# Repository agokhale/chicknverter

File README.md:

# chicknverter
high voltage pwm output stage

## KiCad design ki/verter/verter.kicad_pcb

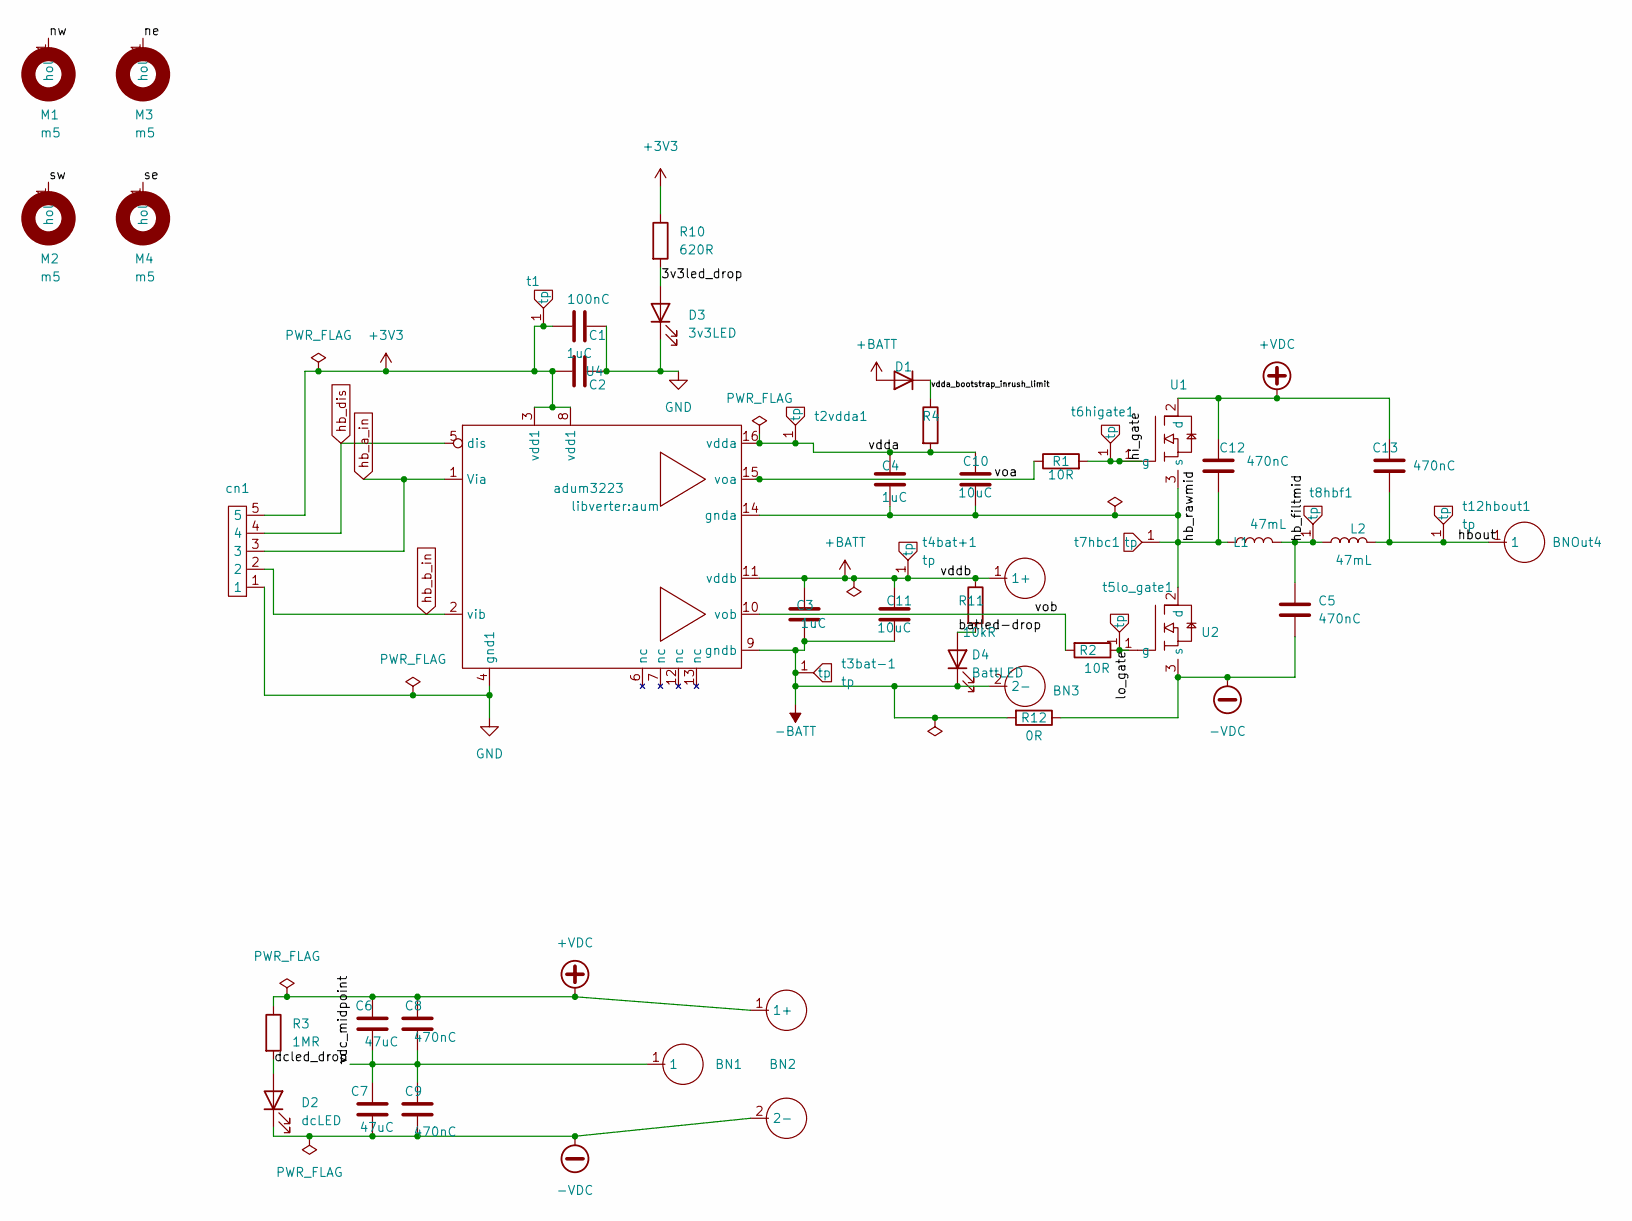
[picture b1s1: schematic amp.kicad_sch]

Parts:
BN1: bana_1; bannaone
BN2, BN3: bana; bannahammuk
BNOut4: bana_1; bannaone
C1: 100nC; C_0603_1608Metric_Pad1.08x0.95mm_HandSolder
C2: 1uC; bettrsmt_polar
C3, C4: 1uC; C_0603_1608Metric_Pad1.08x0.95mm_HandSolder
C5, C8, C9, C12, C13: 470nC; C_2220_5650Metric_Pad1.97x5.40mm_HandSolder
C6, C7: 47uC; epcos-d-25
C10, C11: 10uC; bettrsmt_polar
D1: D; bettrsmt_diode
D2: dcLED; bettrsmt_diode
D3: 3v3LED; bettrsmt_diode
D4: BattLED; bettrsmt_diode
L1, L2: 47mL; Lish
M1, M2, M3, M4: m5; m5mount
R1, R2: 10R; bettrsmt
R3: 1MR; C_0603_1608Metric_Pad1.08x0.95mm_HandSolder
R4: 27R; bettrsmt
R10: 620R; C_0603_1608Metric_Pad1.08x0.95mm_HandSolder
R11: 10kR; C_0603_1608Metric_Pad1.08x0.95mm_HandSolder
R12: 0R; bettrsmt
U1, U2: (no value)
U4: adum3223; aum
cn1: jumper5; jumper.1x5
t1, t2vdda1, t3bat-1, t4bat+1, t5lo_gate1, t6higate1, t7hbc1, t8hbf1, t12hbout1: tp

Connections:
+3V3: C1.1, C2.1, R10.1, U4.3 (vdd1), U4.8 (vdd1), cn1.5, t1.1 (tp)
+BATT: BN3.1 (1+), C3.1, C11.1, D1.2 (A), R11.1, U4.11 (vddb), t4bat+1.1 (tp)
+VDC: BN2.1 (1+), C6.1, C8.1, C12.1, C13.1, R3.1, U1.2 (d)
-BATT: BN3.2 (2-), C3.2, C11.2, D4.1 (K), R12.2, U4.9 (gndb), t3bat-1.1 (tp)
-VDC: BN2.2 (2-), C5.2, C7.2, C9.2, D2.1 (K), R12.1, U2.3 (s)
/amp/3v3led_drop: D3.2 (A), R10.2
/amp/batled-drop: D4.2 (A), R11.2
/amp/dcled_drop: D2.2 (A), R3.2
/amp/hb_filtmid: C5.1, L1.2, L2.1, t8hbf1.1 (tp)
/amp/hb_rawmid: C4.2, C10.2, C12.2, L1.1, U1.3 (s), U2.2 (d), U4.14 (gnda), t7hbc1.1 (tp)
/amp/hbout: BNOut4.1, C13.2, L2.2, t12hbout1.1 (tp)
/amp/hi_gate: R1.2, U1.1 (g), t6higate1.1 (tp)
/amp/lo_gate: R2.1, U2.1 (g), t5lo_gate1.1 (tp)
/amp/ne: M3.1 (hol)
/amp/nw: M1.1 (hol)
/amp/se: M4.1 (hol)
/amp/sw: M2.1 (hol)
/amp/vdc_midpoint: BN1.1, C6.2, C7.1, C8.2, C9.1
/amp/vdda: C4.1, C10.1, R4.2, U4.16 (vdda), t2vdda1.1 (tp)
/amp/vdda_bootstrap_inrush_limit: D1.1 (K), R4.1
/amp/voa: R1.1, U4.15 (voa)
/amp/vob: R2.2, U4.10 (vob)
GND: C1.2, C2.2, D3.1 (K), U4.4 (gnd1), cn1.1
hb_a_in: U4.1 (Via), cn1.3
hb_b_in: U4.2 (vib), cn1.2
hb_dis: U4.5 (dis), cn1.4

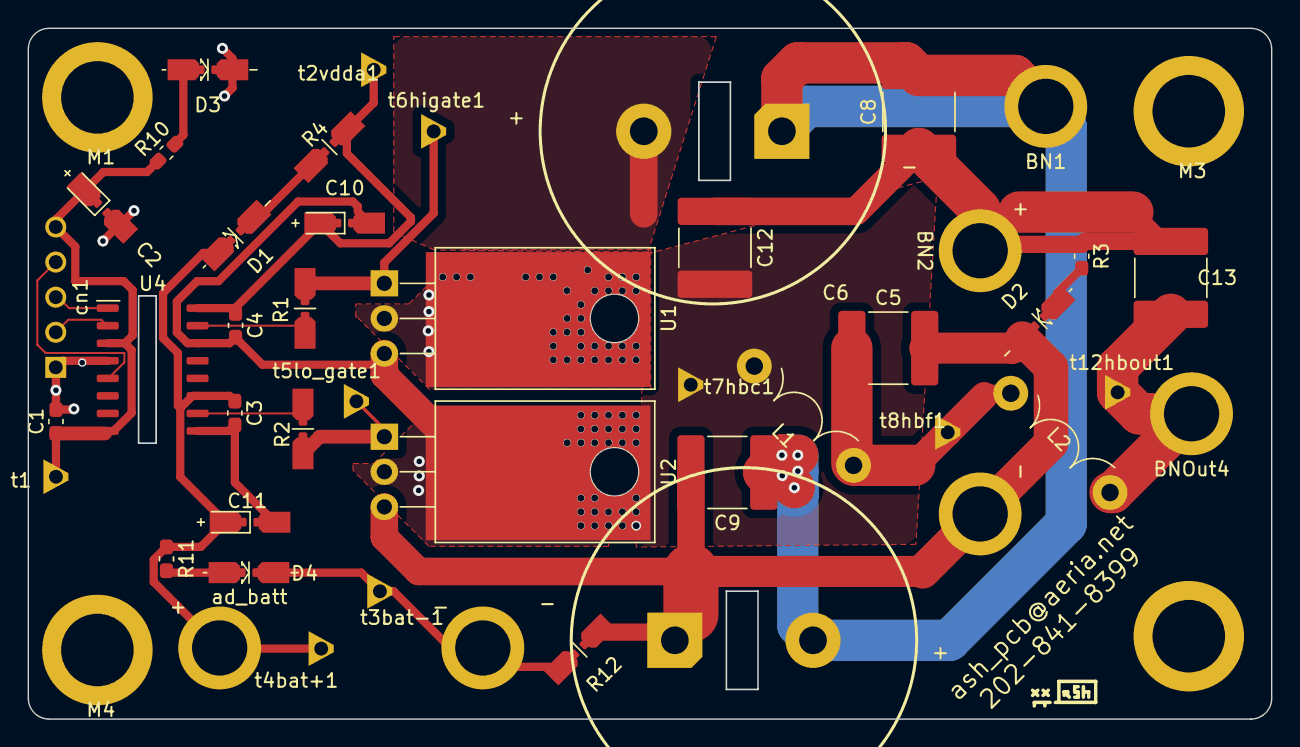
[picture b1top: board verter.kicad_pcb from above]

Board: 4 copper layers, 90.0 x 50.0 mm, 47 parts (0 on the bottom side), 22 nets.

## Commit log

2022-04-30 initial
2022-05-01 ad fp
2022-05-01 kicad goes brrr
2022-06-27 sort
2022-06-27 moar
2022-07-08 add subs
2022-08-01 gerbs in flight!
